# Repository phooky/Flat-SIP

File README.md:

An attempt at a flat version of the Sandin Image Processor.

Rough plan:
* Start with input/sync strip and NTSC encoder modules. If we can get those
  working, the rest is simple.
* Full-size PCB behind Al panels.
* Find original panel size. (4U?)

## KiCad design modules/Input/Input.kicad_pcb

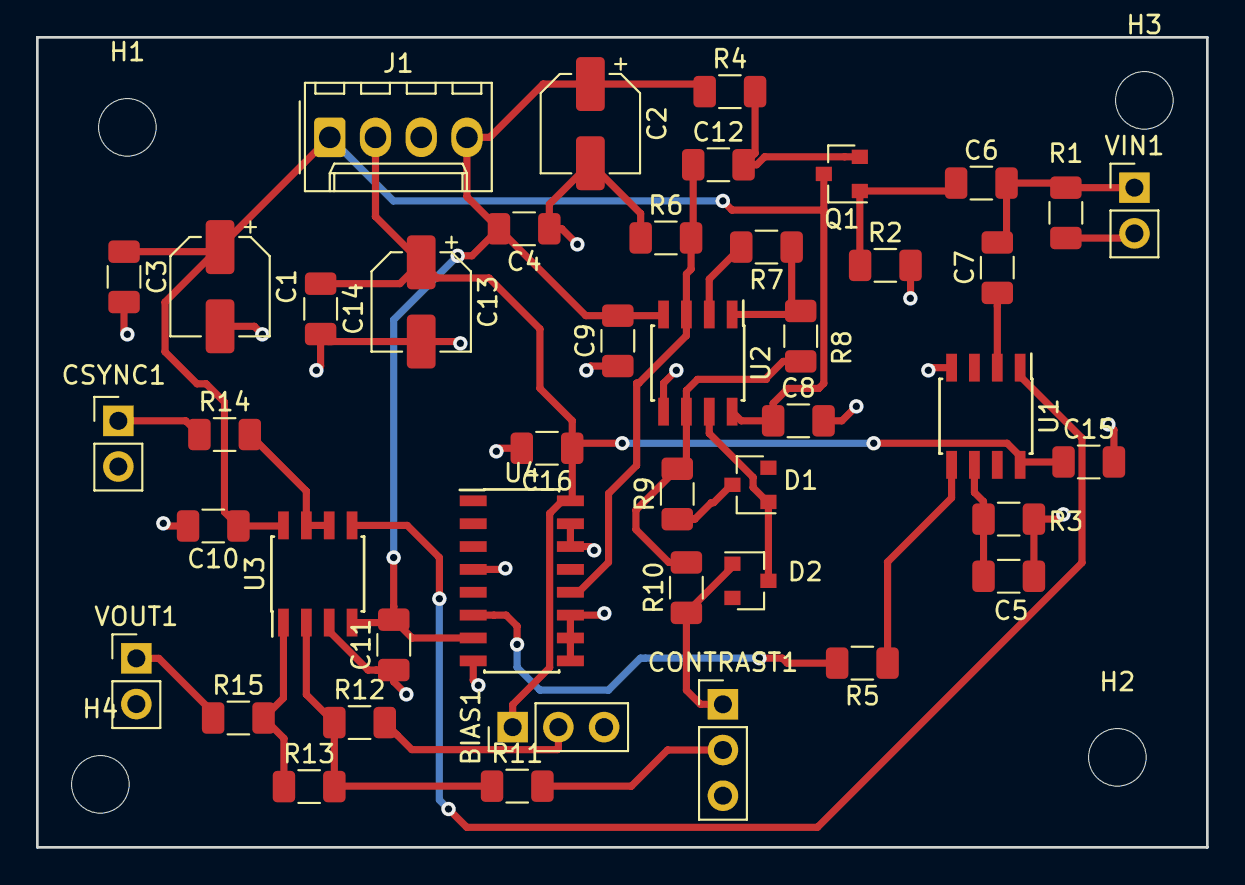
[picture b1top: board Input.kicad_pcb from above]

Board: 2 copper layers, 65.0 x 45.0 mm, 48 parts (0 on the bottom side), 26 nets.

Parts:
BIAS1: 10k; PinHeader_1x03_P2.54mm_Vertical
C1, C2, C13: 10u; CP_Elec_5x5.4
C3, C4: .1u; C_1206_3216Metric
C5, C6, C7, C12, C14, C15, C16: 0.1u; C_1206_3216Metric
C8, C9, C10, C11: .068u; C_1206_3216Metric
CONTRAST1: 10k; PinHeader_1x03_P2.54mm_Vertical
CSYNC1: Conn_Coaxial; PinHeader_1x02_P2.54mm_Vertical
D1, D2: D; D_SOT-23_ANK
H1, H2, H3, H4: MountingHole; MountingHole_3.2mm_M3
J1: Conn_01x04_Male; Molex_KK-254_AE-6410-04A_1x04_P2.54mm_Vertical
Q1: MMBT3904; SOT-23
R1: 75; R_1206_3216Metric
R2, R6: 100k; R_1206_3216Metric
R3: 680k; R_1206_3216Metric
R4, R12, R13: 10k; R_1206_3216Metric
R5, R7, R9, R10: 1k; R_1206_3216Metric
R8: 1.5k; R_1206_3216Metric
R11: 2.7k; R_1206_3216Metric
R14, R15: 500; R_1206_3216Metric
U1: LM1881; SOIC-8_3.9x4.9mm_P1.27mm
U2, U3: LM6172; SOIC-8_3.9x4.9mm_P1.27mm
U4: CD4053B; SOIC-16_3.9x9.9mm_P1.27mm
VIN1: Conn_Coaxial; PinHeader_1x02_P2.54mm_Vertical
VOUT1: Conn_Coaxial; PinHeader_1x02_P2.54mm_Vertical

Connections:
+5V: BIAS1.1, C13.1, C14.1, C15.1, C16.1, J1.2, U1.8, U4.16
+12V: C1.1, C3.1, C8.1, C10.1, J1.1, Q1.3, U2.8, U3.8
-12V: C2.1, C4.2, C9.2, C11.2, J1.4, R4.1, U2.4, U3.4, U4.7
CSYNC: U1.1, U3.5
GND: BIAS1.3, C1.2, C2.2, C3.2, C4.1, C5.2, C8.2, C9.1, C10.2, C11.1, C13.2, C14.2, C15.2, C16.2, CONTRAST1.3, CSYNC1.2, J1.3, R1.2, R2.2, R3.2, R6.1, U1.4, U2.5, U3.3, U4.4, U4.8, U4.9, U4.10, U4.11, U4.14, U4.15, VIN1.2, VOUT1.2
unnamed: BIAS1.2, R12.2
unnamed: C5.1, R3.1, U1.6
unnamed: C6.1, Q1.1, R2.1
unnamed: C6.2, C7.2, R1.1, VIN1.1
unnamed: C7.1, U1.2
unnamed: C12.1, R6.2, U2.3, U4.12
unnamed: C12.2, Q1.2, R4.2
unnamed: CONTRAST1.1, D2.2, R10.1
unnamed: CONTRAST1.2, R11.2
unnamed: CSYNC1.1, R14.1
unnamed: D1.1, R9.1
unnamed: D1.2, D2.1, U2.7
unnamed: R5.1, U1.5
unnamed: R5.2, U4.6
unnamed: R7.1, R8.2, U2.1
unnamed: R7.2, U2.2
unnamed: R8.1, R9.2, R10.2, U2.6
unnamed: R11.1, R12.1, R13.2, U3.2
unnamed: R13.1, R15.2, U3.1
unnamed: R14.2, U3.6, U3.7
unnamed: R15.1, VOUT1.1

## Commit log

2018-10-19 Initial checkin of sync strip and input board
2018-10-19 moving input and sync stripper into its own module
2018-10-19 fix some ERC issues; assign symbols
2018-10-20 added power flags and power connector
2018-10-20 added power pins for opamps and tied inputs of unused amp
2018-10-20 Find and fix missing values
2018-10-21 building out footprints/BOM
2019-03-15 Adding new board based on LZX design
2019-03-15 needs silk but otherwise done for now
2019-03-28 panels added
